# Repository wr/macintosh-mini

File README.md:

<h1 align="center"> Macintosh Mini</h1>

<p align="center">
  <strong>Turn a Maclock alarm clock into a working Mac with a Raspberry Pi</strong>
</p>

<p align="center">
  <a href="https://wells.ee/projects/macintosh-mini/?ref=gh-macintosh-mini">Build guide</a> ⬪
  <a href="#step-2-install-the-software">Install the software</a> ⬪
  <a href="https://shop.wells.ee/products/macintosh-mini/?ref=gh-macintosh-mini">Buy a kit</a> ⬪
  <a href="#donate">Donate</a>
</p>

<p align="center">
  
  <br />
  <a href="https://www.youtube.com/watch?v=zAbAf5-H5Yo">⏵ Watch the full build on YouTube</a>
</p>

---

## What is it?

A [Maclock](https://www.aliexpress.us/w/wholesale-maclock.html) is a cheap alarm clock built into a shockingly accurate miniature Macintosh shell. This project guts one and rebuilds it around a Raspberry Pi Zero running a 68k or PowerPC emulator, so the tiny Mac actually boots System 7, plays the startup chime, and runs vintage software. Buttons, brightness, sound, Wi-Fi, Bluetooth, and battery all work.

## Step 1: Build or buy one

The [build guide](https://wells.ee/projects/macintosh-mini/?ref=gh-macintosh-mini), on my site, covers everything from opening the clock to the first boot: parts, assembly, software, and troubleshooting.

You can [buy a DIY kit or a finished build](https://shop.wells.ee/products/macintosh-mini/?ref=gh-macintosh-mini) from my maker shop. Faster than shipping from China, and your purchase supports the continued development of this project.

## Step 2: Install the software

**You will need:**
- A Mac ROM file (`064DC91D` is a common one to search for)
- A Mac OS disk image with System 7.0 to 8.5. The [BlueSCSI image library](https://bluescsi.com/docs/BlueSCSI-Images) has ready-made ones, or skip it: the installer offers [our Mac OS 8.1 disk](https://archive.org/details/macos-8.1-basilisk-ii)

**Prepare the MicroSD card**
1. Flash **Raspberry Pi OS Lite (64-bit)** to a microSD card with [Raspberry Pi Imager](https://www.raspberrypi.com/software/). Set your Wi-Fi network and turn on SSH in its settings.
2. Rename your Mac ROM file to `ROM`, and copy it and your disk image, if you have one, to the Pi's home folder:

   ```bash
   scp ROM yourdisk.hda <user>@<pi_ip>:~/
   ```

3. SSH into the Pi and run the install script. It asks a few questions, like which startup chime to play, then does the rest:

   ```bash
   curl -fsSL https://raw.githubusercontent.com/wr/macintosh-mini/main/setup.sh | bash
   ```

The Pi automatically restarts into Mac OS when it's done.

You can run the same command again to install future updates.

* * *

_Optional:_ If you want to skip the automatic script and install everything yourself, or see exactly what the script changes:

- [Set up the Pi](maclock-build/): display, audio, brightness dial and buttons.
-  [Install the emulator](emulators/): Basilisk II or SheepShaver.

## Getting help

Open a [GitHub issue](https://github.com/wr/macintosh-mini/issues) — I'm happy to help, and very responsive!

## Credits

Startup chimes and crash sounds are mirrored from D. Schaub's Apple Sounds collection at <https://froods.ca/~dschaub/sound.html>. All sounds are © Apple, Inc.

## Donate

While this project is free and open source, donations are deeply appreciated, and make ongoing development and support possible.
[Donate now](https://www.buymeacoffee.com/wellsworkshop)

## License

Copyright © 2026 Wells Riley.

- **Hardware** (the boards, the bezel and the USB port jig): [CERN-OHL-S-2.0](./LICENSES/CERN-OHL-S-2.0.txt)
- **Software** ([`setup.sh`](./setup.sh) and [`maclock-build/`](./maclock-build/)): [GPL-3.0-or-later](./LICENSES/GPL-3.0-or-later.txt)
- **Everything else** (docs, drawings, photos): [CC BY-SA 4.0](./LICENSES/CC-BY-SA-4.0.txt)

The [Mac chimes](./emulators/chimes/) are Apple's and the display overlay is Waveshare's; neither is covered. [`REUSE.toml`](./REUSE.toml) maps every file.

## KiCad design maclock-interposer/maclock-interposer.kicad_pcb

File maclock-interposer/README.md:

# Macintosh Mini GPIO interposer

A 52 × 27.4 mm, 2-layer KiCad 10 board that sits on the 40-pin header between the Pi Zero 2 W and the Waveshare 2.8" DPI display. Order it fully assembled — no soldering, and no bent, cut, or desoldered pins on the Pi.

An SMD socket underneath plugs onto the Pi and an SMD pin header on top plugs into the display. 35 pins pass straight through (one via each); the five GPIOs the [breakout PCB](../maclock-pcb/) uses (header pins 13, 19, 23, 35, 37) connect to the Pi side **only** and never reach the display, which otherwise fights the dial and buttons. Those five plus 5V and GND come out on a straight 1×7 female socket (J2) on the screen side at the GPIO 21 end, in the same order as the breakout's `Pi GPIO` header, so one straight 1×7 male-to-female Dupont cable connects the two.

The board is drawn the way it sits in the Maclock: Pi mounted upside-down, seen from the screen. Order it with **blue solder mask and white silkscreen** — the screen side is inverted (silk is the background, the lettering is bare mask); branding is on the Pi side, and J2's pin labels are on both sides.

| J2 pin | Silk   | Net   | Pi header pin | GPIO |
| ------ | ------ | ----- | ------------- | ---- |
| 1      | Dial B | ENC_B | 19            | 10   |
| 2      | GND    | GND   | 20 (all GNDs) | —    |
| 3      | Dial A | ENC_A | 23            | 11   |
| 4      | 5V     | 5V    | 2, 4          | —    |
| 5      | A+     | AUDIO | 35            | 19   |
| 6      | SW2    | BTN2  | 37            | 26   |
| 7      | SW1    | BTN1  | 13            | 27   |

## Bill of materials

| Ref | Qty | Part                                                                  | LCSC                                                                  | Notes                                             |
| --- | --- | --------------------------------------------------------------------- | --------------------------------------------------------------------- | ------------------------------------------------- |
| J1  | 1   | 2×20 female socket, 2.54 mm, SMD, 8.5 mm — Hong Cheng `HC-PM254-8.5H-2x20PS` | [`C22436166`](https://www.lcsc.com/product-detail/C22436166.html) | **Bottom** side, plugs onto the Pi                |
| J3  | 1   | 2×20 pin header, 2.54 mm, SMD — Hanbo `HB-PH9-254220PB2GOP`            | [`C6332245`](https://www.lcsc.com/product-detail/C6332245.html)       | Top side, plugs into the display                  |
| J2  | 1   | 1×7 female header (socket), 2.54 mm, 8.5 mm, THT — XFCN `PM254V-11-07-H85` | [`C2832270`](https://www.lcsc.com/product-detail/C2832270.html) | Top (screen) side |

Both sides carry parts, so order two-sided assembly. Before ordering, check the J1/J3 drawings for locating pegs — the footprints are KiCad's generic peg-less SMD lands (3.0 / 3.15 × 1.0 mm pads, ±2.52 mm from the centreline).

## Use

Stack Pi → interposer → display (silk: `THIS SIDE FACING PI` / `THIS SIDE FACING SCREEN`). Run a straight 1×7 male-to-female Dupont cable from J2 to the breakout's `Pi GPIO` header, pin 1 (`Dial B`, square pad, GPIO 21 end) to pin 1 (`Dial B`).

The interposer adds about 12.5 mm between the Pi and the display (8.5 mm socket + 1.6 mm PCB + 2.5 mm header base), and the board reaches ~10.5 mm past the Pi's header edge. J2 stands 8.5 mm off the screen side, and the Dupont plug in it points toward the display — check both against your case and the display board before ordering.

## License

CERN-OHL-S-2.0, same as the [breakout PCB](../maclock-pcb/README.md#license) — see [`LICENSE`](./LICENSE).

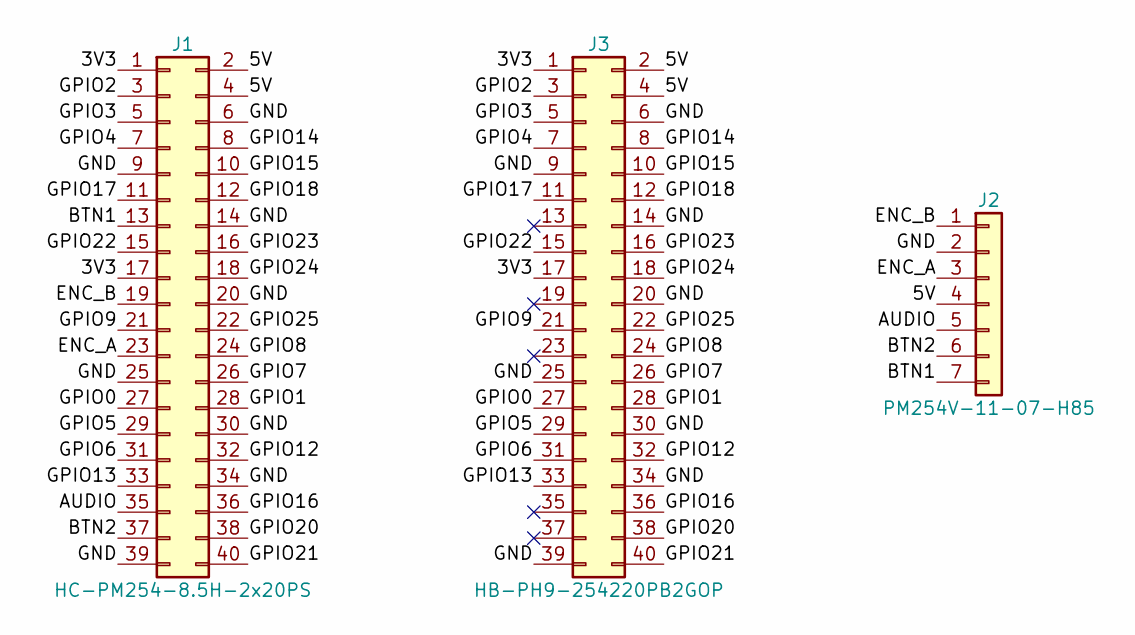
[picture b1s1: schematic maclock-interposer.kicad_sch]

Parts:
J1: HC-PM254-8.5H-2x20PS; PinSocket_2x20_P2.54mm_Vertical_SMD; MPN HC-PM254-8.5H-2x20PS; LCSC C22436166
J2: PM254V-11-07-H85; PinSocket_1x07_P2.54mm_Vertical; MPN PM254V-11-07-H85; LCSC C2832270
J3: HB-PH9-254220PB2GOP; PinHeader_2x20_P2.54mm_Vertical_SMD; MPN HB-PH9-254220PB2GOP; LCSC C6332245

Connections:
/3V3: J1.1, J1.17, J3.1, J3.17
/5V: J1.2, J1.4, J2.4, J3.2, J3.4
/AUDIO: J1.35, J2.5
/BTN1: J1.13, J2.7
/BTN2: J1.37, J2.6
/ENC_A: J1.23, J2.3
/ENC_B: J1.19, J2.1
/GND: J1.6, J1.9, J1.14, J1.20, J1.25, J1.30, J1.34, J1.39, J2.2, J3.6, J3.9, J3.14, J3.20, J3.25, J3.30, J3.34, J3.39
/GPIO0: J1.27, J3.27
/GPIO1: J1.28, J3.28
/GPIO2: J1.3, J3.3
/GPIO3: J1.5, J3.5
/GPIO4: J1.7, J3.7
/GPIO5: J1.29, J3.29
/GPIO6: J1.31, J3.31
/GPIO7: J1.26, J3.26
/GPIO8: J1.24, J3.24
/GPIO9: J1.21, J3.21
/GPIO12: J1.32, J3.32
/GPIO13: J1.33, J3.33
/GPIO14: J1.8, J3.8
/GPIO15: J1.10, J3.10
/GPIO16: J1.36, J3.36
/GPIO17: J1.11, J3.11
/GPIO18: J1.12, J3.12
/GPIO20: J1.38, J3.38
/GPIO21: J1.40, J3.40
/GPIO22: J1.15, J3.15
/GPIO23: J1.16, J3.16
/GPIO24: J1.18, J3.18
/GPIO25: J1.22, J3.22

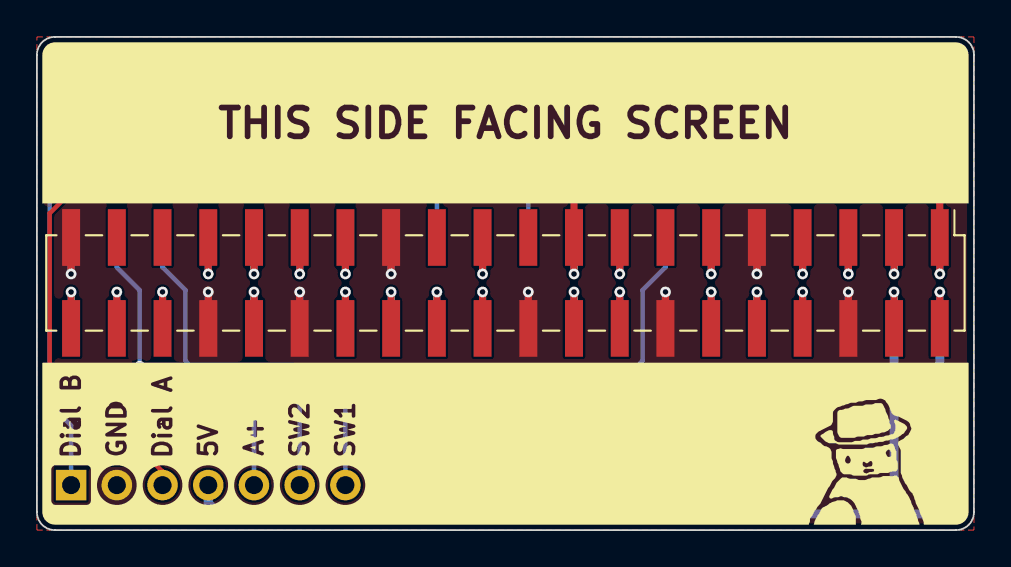
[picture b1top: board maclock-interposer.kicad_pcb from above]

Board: 2 copper layers, 52.1 x 27.4 mm, 3 parts (1 on the bottom side), 31 nets.

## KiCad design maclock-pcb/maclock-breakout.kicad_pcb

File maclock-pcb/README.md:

# Macintosh Mini breakout PCB

KiCad 10 project for the breakout that connects the Mac-shaped clock's front-panel parts (rotary encoder, two pushbuttons, speaker, power switch and battery harness) to the Pi Zero 2 W. The PAM8302A audio amplifier is on the board itself. Current revision: 2026.11, which rebuilds the Pi's audio signal on the board and gives the Pi's supply current its own ground return (see [Design notes](#design-notes)); rev 2026.09 boards, the ones that shipped, work but whine faintly with the Pi running.

Wiring it to the Pi, with pin assignments, is [step 2 of the build guide](https://wells.ee/projects/macintosh-mini/#2-connect-the-pi-to-the-screen-and-the-board). For the case-side parts you'll print, see the [3D-printed screen bezel](../maclock-screen-bezel/).

Order from [PCBway](https://www.pcbway.com/project/shareproject/W654223ASS41_Untitled_kicad_pcb_95cca7e3.html). You can [use my referral code](https://pcbway.com/g/AsfKU9) to get $5 off your order, if you want.

## Bill of materials

To populate one board. Every part except ENC1 is stocked at LCSC, so PCBway can assemble the board with ENC1 left off; it is out of the BOM and placement files, so fit it yourself afterwards. Only the Pi header is through-hole. The DigiKey column is for hand assembly: where DigiKey does not carry the LCSC part, a drop-in equivalent is named.

| Ref | Qty | Part | DigiKey (hand assembly) | Notes |
| --- | --- | --- | --- | --- |
| C1 | 1 | 10 nF X7R 0603 — FH `0603B103K500NT` (LCSC [`C57112`](https://www.lcsc.com/product-detail/C57112.html)) | [`1276-1009-1-ND`](https://www.digikey.com/en/products/result?keywords=1276-1009-1-ND) Samsung `CL10B103KB8NNNC` | Audio low-pass with R3 |
| C2, C3 | 2 | 220 nF X7R 0603 — Samsung `CL10B224KA8NNNC` (LCSC [`C21120`](https://www.lcsc.com/product-detail/C21120.html)) | [`1276-1111-1-ND`](https://www.digikey.com/en/products/result?keywords=1276-1111-1-ND) | Amp input coupling (IN+ and IN−) |
| C4, C8, C10 | 3 | 1 µF X5R 0603 — Samsung `CL10A105KB8NNNC` (LCSC [`C15849`](https://www.lcsc.com/product-detail/C15849.html)) | [`478-KGM15BR51E105KTCT-ND`](https://www.digikey.com/en/products/result?keywords=478-KGM15BR51E105KTCT-ND) KYOCERA AVX `06033D105KAT2A` (25 V) | Amp supply decoupling (C4); U3 input (C8); U3 output and U2 supply (C10) |
| C5 | 1 | 10 µF X5R 0805 — Samsung `CL21A106KAYNNNE` (LCSC [`C15850`](https://www.lcsc.com/product-detail/C15850.html)) | [`490-16824-1-ND`](https://www.digikey.com/en/products/result?keywords=490-16824-1-ND) Murata `GRM21BR61E106KA73K` | Amp bulk decoupling |
| C6 | 0 | 470 pF C0G 0402 — Samsung `CL05C471JB5NNNC` (LCSC [`C307449`](https://www.lcsc.com/product-detail/C307449.html)) | [`1276-1117-1-ND`](https://www.digikey.com/en/products/result?keywords=1276-1117-1-ND) | **Not fitted**, left off the BOM and placement file. Optional second filter pole across the amp inputs, between R4 and R5 (see [Design notes](#design-notes)) |
| ENC1 | 1 | Rotary encoder, HUANO 4.5 mm mouse-wheel type, laid on its back with the hex bore up — sold as MECCANIXITY on [Amazon](https://www.amazon.com/dp/B0C13ZZVT5) (10-pack) and on [AliExpress](https://www.aliexpress.us/item/3256805576298875.html) (choose 4.5MM); not stocked at LCSC, DigiKey or Mouser | — (no equivalent at DigiKey) | The dial. Body 9.54 × 8.34 × 4.15 mm, 1.74 mm hex bore, 2.5 mm pin pitch. **Fitted by hand**, left out of the BOM and placement file: lay it on its black back over the bore with the marked metal face up and the pins north, bend the pins down onto their pads and solder, and do the same with the two clip legs on the MP pads for strength. Seen from the marked face with the pins down, the common pin is on the left, as on TT's and HOAUC's mouse-wheel encoders, so face up it lands on C, the east pad |
| J1 | 1 | Molex PicoBlade 1×2, 1.25 mm, SMD top entry — `53398-0271` (LCSC [`C122410`](https://www.lcsc.com/product-detail/C122410.html)) | [`WM7606CT-ND`](https://www.digikey.com/en/products/result?keywords=WM7606CT-ND) | **Power switch**, in series with the battery supply; silkscreened "Switch". Takes the Maclock's 2-wire switch plug |
| J2 | 1 | Molex PicoBlade 1×4, 1.25 mm, SMD top entry — `53398-0471` (LCSC [`C17617036`](https://www.lcsc.com/product-detail/C17617036.html)) | [`WM7608CT-ND`](https://www.digikey.com/en/products/result?keywords=WM7608CT-ND) | **Power input**, silkscreened "Power". Takes the Maclock's 4-wire plug: pin 1 (silk `+`) = battery supply, about 4 V (the clock's charging board passes the cell through, it does not boost it), pin 2 (silk `-`) = GND, pins 3–4 unused |
| J3 | 1 | Molex PicoBlade 1×2, 1.25 mm, SMD top entry — `53398-0271` (LCSC [`C122410`](https://www.lcsc.com/product-detail/C122410.html)) | [`WM7606CT-ND`](https://www.digikey.com/en/products/result?keywords=WM7606CT-ND) | **Speaker**, silkscreened "Speaker". Same part as J1; polarity does not matter |
| J4 | 1 | 1×7 male pin header, 2.54 mm — XFCN `PZ254V-11-07P` (LCSC [`C492406`](https://www.lcsc.com/product-detail/C492406.html)) | [`35-PRPC007SAAN-RC-ND`](https://www.digikey.com/en/products/result?keywords=35-PRPC007SAAN-RC-ND) Sullins `PRPC007SAAN-RC` | Through-hole, silkscreened "Pi GPIO". Pin order: Dial B, GND, Dial A, 5V, A+, SW2, SW1 |
| R1, R2 | 2 | 1 kΩ ±1% 0402 — UNI-ROYAL `0402WGF1001TCE` (LCSC [`C11702`](https://www.lcsc.com/product-detail/C11702.html)) | [`311-1.00KLRCT-ND`](https://www.digikey.com/en/products/result?keywords=311-1.00KLRCT-ND) Yageo `RC0402FR-071KL` | In series with the SW1 and SW2 button lines |
| R3 | 1 | 1 kΩ ±1% 0402 — same as above | same as above | With C1, the 16 kHz low-pass on the rebuilt PWM audio |
| R4, R5 | 2 | 47 kΩ ±1% 0402 — UNI-ROYAL `0402WGF4702TCE` (LCSC [`C25792`](https://www.lcsc.com/product-detail/C25792.html)) | [`311-47.0KLRCT-ND`](https://www.digikey.com/en/products/result?keywords=311-47.0KLRCT-ND) Yageo `RC0402FR-0747KL` | Amp input resistors, set the gain to about 8 dB |
| R6 | 1 | 100 kΩ ±1% 0402 — UNI-ROYAL `0402WGF1003TCE` (LCSC [`C25741`](https://www.lcsc.com/product-detail/C25741.html)) | [`311-100KLRCT-ND`](https://www.digikey.com/en/products/result?keywords=311-100KLRCT-ND) Yageo `RC0402FR-07100KL` | Pull-up on the amp's shutdown pin (amp always on) |
| SW1, SW2 | 2 | BZCN `TSB001A3518A` side-press SMD tactile, 7.7 × 3.55 mm, 180 gf (LCSC [`C2888448`](https://www.lcsc.com/product-detail/C2888448.html)) | [`2223-TS32-7-35-BK-B-160-RA-SMT-TRCT-ND`](https://www.digikey.com/en/products/result?keywords=2223-TS32-7-35-BK-B-160-RA-SMT-TRCT-ND) Same Sky `TS32-7-35-BK-B-160-RA-SMT-TR`: same land (its pegs, shell pads and 4.2 mm signal pitch match; the signal pads sit 0.15 mm closer to the pegs), but 160 gf, and the button sits about 0.15 mm lower and 0.2 mm further out. Not yet tried in the case | The two front buttons |
| U1 | 1 | PAM8302A 2.5 W class-D mono amp, MSOP-8 — Diodes `PAM8302AASCR` (LCSC [`C113367`](https://www.lcsc.com/product-detail/C113367.html)) | [`PAM8302AASCRDICT-ND`](https://www.digikey.com/en/products/result?keywords=PAM8302AASCRDICT-ND) | Bottom side |
| U2 | 1 | Single Schmitt-trigger buffer, SOT-23-5 — TI `SN74LVC1G17DBVR` (LCSC [`C7836`](https://www.lcsc.com/product-detail/C7836.html)) | [`296-11933-1-ND`](https://www.digikey.com/en/products/result?keywords=296-11933-1-ND) | Rebuilds the Pi's PWM audio from U3's 3.0 V |
| U3 | 1 | 3.0 V low-noise LDO, SOT-23-5 — TI `TPS7A2030PDBVR` (LCSC [`C963429`](https://www.lcsc.com/product-detail/C963429.html)) | [`296-TPS7A2030PDBVRCT-ND`](https://www.digikey.com/en/products/result?keywords=296-TPS7A2030PDBVRCT-ND) | Quiet 3.0 V for U2 and the shutdown pull-up |
| — | 1 | Small speaker, 8 Ω, 1 W, 28–40 mm, PicoBlade 1.25 mm 2-pin plug (often sold as "JST 1.25"), e.g. [Adafruit 3923](https://www.adafruit.com/product/3923) | — | Whatever fits behind the Maclock grille |

The schematic carries the same data in each symbol's `Manufacturer`, `MPN`, `LCSC` and (for ENC1) `Supplier` / `Supplier Link` fields, so any BOM exported from it includes ENC1's source, though ENC1 itself is left out of the BOM.

## Design notes

**Audio input.** The Pi's audio is PWM on GPIO 19, switching between the Pi's own 3.3 V and ground, so it carries whatever noise the Pi's supply and ground do. U2 rebuilds it from U3, a separate low-noise 3.0 V regulator (net `+3V0`), so only the timing of the Pi's signal reaches the amp. U3 runs from the clock's battery, which is about 4 V at full charge and falls as it drains, so it is a 3.0 V part rather than 3.3 V: that keeps it far enough above its dropout to keep filtering as the battery runs down. It works just as well from a real 5 V. R3/C1 then low-pass it at 16 kHz.

**Amplifier.** The filtered signal goes C2 → R4 → PAM8302A IN+, with IN− terminated through the matching R5/C3 pair. R4 adds to the chip's internal 10 kΩ input resistor, which brings its fixed 23.5 dB gain down to about 8 dB; fine volume is a software setting, and `setup.sh` leaves 4 dB of headroom so the startup chime's peaks don't clip. The shutdown pin is pulled up through R6 so the amp is always on (no header GPIO is free for a mute).

C6 is a spare pad, not fitted. R3/C1 is a single pole, which takes only about 24 dB off the Pi's PWM noise near the amp's own 200–300 kHz switching frequency, where a class-D amp can fold it back into the audio band as hiss or a faint whistle. A 470 pF across IN+ and IN− adds a second pole at about 20 kHz (with R4/R5 and the chip's internal 10 kΩ), for roughly 46 dB there, at the cost of about 1 dB at 10 kHz. The rev 2026.09 boards have the same single pole and none of their measured noise came from it, so solder C6 on only if a board hisses or whistles with the amp warm.

**Grounds.** The Pi, its display and its backlight draw up to about 1 A, and the return current comes back on its own trace (net `GND_PI`) from J4 pin 2 to J2, where the net tie NT1 joins it to the board ground. On earlier revisions that current flowed through the amp's ground and the amp shared the Pi's supply copper, which put a faint whine in the speaker of the rev 2026.09 boards: a 1 kHz comb from the backlight PWM, plus drifting tones from the emulator's load. NT1 is copper only, so it is not in the BOM. The amp now takes its supply straight from J1, so it no longer shares the Pi's supply trace, and its 1 µF decoupling capacitor sits right against its supply and ground pins.

**Dial and buttons.** ENC1's A and B go straight to GPIO 11 and GPIO 10, and the buttons through R1/R2 to GPIO 27 and GPIO 26; the Pi's internal pull-ups do the rest (see [`brightness_control.py`](../maclock-build/brightness_control.py)). ENC1 lies on its back with its bore over the dial's shaft and its pins pointing north; its footprint origin is the bore. HUANO publishes no drawing, so the land is drawn from a measured part: the bore is 4.5 mm from the pin edge and the pins are 3 mm long, and the pads run from just outside the body to the pin tips. Lying flat, it stands 4.15 mm tall.

**Libraries.** Two project libraries ship with the board, next to the KiCad 10 standard libraries:

- `maclock` — ENC1's symbol and footprint, drawn for this project because the encoder lies on its back and has no published land pattern. There is no 3D model for it.
- `lcsc` — LCSC's own symbol, footprint and 3D model for SW1/SW2 (C2888448), imported with `easyeda2kicad --full --lcsc_id=C2888448`. easyeda2kicad's conversion artefacts were fixed, nothing else: the plastic-peg holes are NPTH, the bracket pads have no outline stroke (so the copper is LCSC's 1.5 mm), the pins are passive, and the courtyard is one closed outline.

## Fabrication files

Gerbers, drill files, the placement file and the BOM are generated with `kicad-cli` into `production/`, which git ignores:

```sh
K=/Applications/KiCad/KiCad.app/Contents/MacOS/kicad-cli
mkdir -p production/gerbers
$K pcb export gerbers -l "F.Cu,B.Cu,F.Paste,B.Paste,F.Silkscreen,B.Silkscreen,F.Mask,B.Mask,Edge.Cuts" -o production/gerbers/ maclock-breakout.kicad_pcb
$K pcb export drill --format excellon --excellon-separate-th -o production/gerbers/ maclock-breakout.kicad_pcb
(cd production && zip -qj maclock-breakout-gerbers.zip gerbers/* && rm -r gerbers)
$K pcb export pos --format csv --units mm --side both -o production/maclock-breakout-positions.csv maclock-breakout.kicad_pcb
$K sch export bom --fields 'Reference,${QUANTITY},Value,Footprint,Manufacturer,MPN,LCSC,Supplier,Supplier Link' \
  --group-by 'Value,Footprint,MPN' -o production/maclock-breakout-bom.csv maclock-breakout.kicad_sch
```

## License

CERN-OHL-S-2.0 — see [`LICENSE`](./LICENSE). You can make, modify and sell the board. Boards you make must point to their source, and a modified design must be published under the same licence.

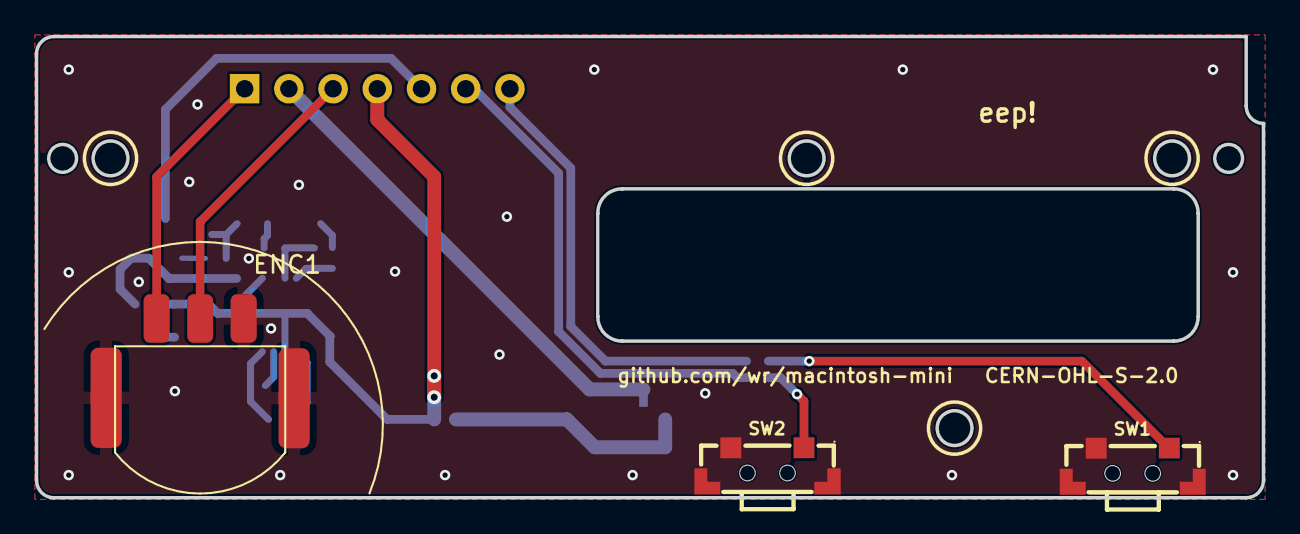
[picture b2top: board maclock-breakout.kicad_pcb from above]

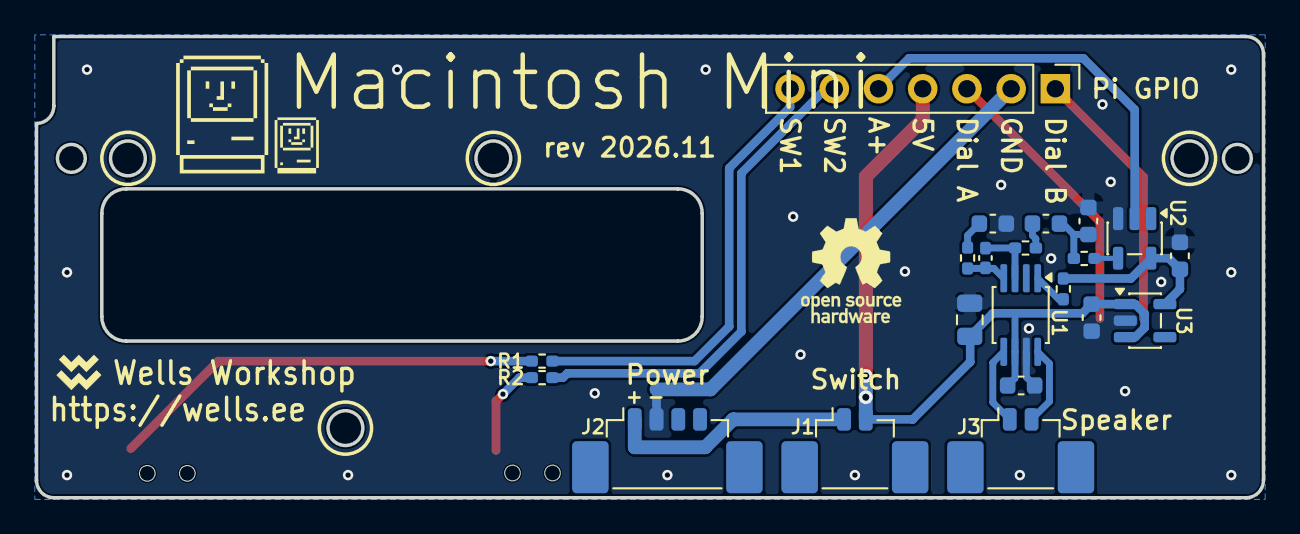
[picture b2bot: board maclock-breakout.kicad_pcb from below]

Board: 2 copper layers, 70.5 x 26.5 mm, 26 parts (23 on the bottom side), 21 nets.

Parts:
C1: 10nF; C_0603_1608Metric
C2, C3: 220nF; C_0603_1608Metric
C4, C8, C10: 1uF; C_0603_1608Metric
C5: 10uF; C_0805_2012Metric
C6: 470pF; C_0402_1005Metric_Pad0.74x0.62mm_HandSolder
ENC1: HUANO 4.5; RotaryEncoder_HUANO_4.5mm_LayFlat_SMD
J1, J3: 53398-0271; Molex_PicoBlade_53398-0271_1x02-1MP_P1.25mm_Vertical
J2: 53398-0471; Molex_PicoBlade_53398-0471_1x04-1MP_P1.25mm_Vertical
J4: Pi GPIO; PinHeader_1x07_P2.54mm_Vertical
LOGO1: OSHW-Logo_5.7x6mm_SilkScreen
NT1: NetTie_2; NetTie-2_SMD_Pad0.5mm
R1, R2, R3: 1k; R_0402_1005Metric_Pad0.72x0.64mm_HandSolder
R4, R5: 47k; R_0402_1005Metric_Pad0.72x0.64mm_HandSolder
R6: 100k; R_0402_1005Metric_Pad0.72x0.64mm_HandSolder
SW1, SW2: TSB001A3518A; SW-SMD_TSB001XXXX
U1: PAM8302AASCR; MSOP-8_3x3mm_P0.65mm
U2: SN74LVC1G17DBVR; SOT-23-5
U3: TPS7A2030PDBVR; SOT-23-5

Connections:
+3V0: C10.1, R6.1, U2.5, U3.5
+5V: C4.1, C5.1, C8.1, J1.2, J4.4, U1.6, U3.1, U3.3
/5V_IN: J1.1, J2.1
/A+: C1.1, C2.1, R3.2
/AMP_SD: R6.2, U1.1
/AUDIO: J4.5, U2.2
/BTN1: J4.7, R1.1
/BTN2: J4.6, R2.1
/ENC_A: ENC1.A, J4.3
/ENC_B: ENC1.B, J4.1
/GND_PI: J4.2, NT1.1
/SPK+: J3.1, U1.5
/SPK-: J3.2, U1.8
/SW1: R1.2, SW1.1
/SW2: R2.2, SW2.1
GND: C1.2, C3.1, C4.2, C5.2, C8.2, C10.2, ENC1.C, ENC1.MP, J2.2, NT1.2, SW1.2, SW1.3, SW1.4, SW2.2, SW2.3, SW2.4, U1.7, U2.3, U3.2
unnamed: C2.2, R4.1
unnamed: C3.2, R5.1
unnamed: R3.1, U2.4
unnamed: C6.1, R4.2, U1.3
unnamed: C6.2, R5.2, U1.4

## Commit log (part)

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2026-05-14 updated board design to 2026.5
2026-05-28 Add BasiliskII (68k) install path for leaner emulation on Pi Zero 2 W
    SheepShaver interprets PowerPC on the Zero 2 W's Cortex-A53 (its JIT is
    x86-only), which is the worst case for this hardware. Emulating a 68k Mac
    (System 7) via BasiliskII is far cheaper to interpret, so add it as a
    parallel install path and make it the default in the menu, keeping
    SheepShaver selectable for PPC-era software.
    Tuning follows the proven MacintoshPi-on-Zero-2-W config: frameskip 2,
2026-05-28 BasiliskII: add --rom flag, libmpfr-dev dep, autostart switching, debug-exit fix
    Shaken out by an end-to-end install on the actual Pi Zero 2 W:
    - --rom <file>: a Pi may already hold a 4 MB PPC ROM named "ROM"; the 68k
    ROM needs explicit selection (the default "ROM" would be the wrong one).
    - libmpfr-dev: BasiliskII's FPU core compiles with -DFPU_MPFR and won't
    build on a fresh Pi without the MPFR headers.
    - Each emulator's profile patch now strips the other's autostart block, so
2026-05-28 Add kiosk lifecycle controls; make re-runs update/switch-safe
    - Reset button double-press force-quits the emulator to a Pi prompt;
    button_handler gains debounce-aware single vs double dispatch.
    - Launcher keys off the emulator's exit status: 0 (Mac "Shut Down") or
    143 (double-reset) drop to a Pi prompt, anything else relaunches.
    Mac "Restart" reboots the VM in place, so it auto-reboots for free.
    - Add a `macintosh` command to (re)boot the Mac from a shell.
2026-05-28 Enable VOSF for BasiliskII
    VOSF re-blits only changed screen regions instead of the whole frame
    every tick — noticeably snappier UI. Verified stable on the Pi Zero 2 W
    (aarch64), so drop the old --disable-vosf workaround.
    Refs: W-247
2026-05-28 Add boot preflight for missing/unconfigured ROM or disk
    New /usr/local/bin/mac-preflight runs before the emulator: if the
    configured ROM+disk are present it boots; if not, it auto-fills the
    prefs when exactly one ROM (matched by size) and one disk image exist
    in $HOME; otherwise it prints what's missing/ambiguous and drops to a
    prompt instead of failing cryptically. Wired into both launchers.
    Refs: W-247, W-266
2026-05-28 README: list which disk image formats work
    Most people grab an image online; spell out what mounts (raw hard-disk
    images, any extension; sparsebundle) and what doesn't (.dmg/.smi/.toast,
    still-zipped files).
    Refs: W-247
2026-05-28 Reorganize emulator guides into emulators/; default networking
    - Move the manual guides into emulators/ (SheepShaver.md, BasiliskII.md)
    next to the shared chimes/, with an index README. Adds a BasiliskII
    manual guide that was missing.
    - Add `ether slirp` to both prefs so networking works out of the box.
    - Accuracy + path fixes across all READMEs (BasiliskII is the default,
    button single/double behavior, disk formats, updated cross-links and
2026-05-28 Tidy manual-install wording in READMEs
    Bullet the root README's manual-install guide links and trim the
    maclock-build emulator paragraph.
    Refs: W-247
2026-05-28 Stop tracking KiCad fp-lib-table
    It pinned KiCad to a machine-specific absolute path. Remove it and
    gitignore the project-local KiCad lib tables.
2026-05-28 Add BasiliskII (68k) emulator as default
    * Add BasiliskII (68k) install path for leaner emulation on Pi Zero 2 W
    SheepShaver interprets PowerPC on the Zero 2 W's Cortex-A53 (its JIT is
    x86-only), which is the worst case for this hardware. Emulating a 68k Mac
    (System 7) via BasiliskII is far cheaper to interpret, so add it as a
    parallel install path and make it the default in the menu, keeping
    SheepShaver selectable for PPC-era software.
2026-05-28 setup: clearer install menu
    Replace the cryptic "Both" default with self-describing options, a blank
    separator after the recommended choice, and widen the menu box to fit.
    Refs: W-269
2026-05-28 docs: write the product name as "Basilisk II" (with a space)
    Apply the spaced name in user-facing prose and the install-menu labels.
    The binary, paths, commands, and the BasiliskII.md filename/links are
    left as-is.
    Refs: W-269
2026-05-28 setup: reconfigure menu for existing installs
    When prefs already exist for the chosen emulator, offer a keep-or-change
    menu (disk image, startup chime, color depth) instead of silently keeping
    everything. Changes are applied in place; fresh-install flow unchanged.
    Refs: W-270
2026-05-28 setup: polish installer and settings menus
    - Install menu: title "Macintosh Mini Installer", no prompt line, no
    blank separator, shorter labels.
    - Emulator Settings: drop the "Keep" row; OK=<Change> the highlighted
    setting, Cancel=<Continue> to proceed; show current values; title
    "Emulator Settings". Persist the chosen chime so its value can show.
    - Shorten the performance prompt text.
2026-05-28 setup: colons + full labels in settings, clearer perf prompt
    Emulator Settings rows read "Disk image:/Startup chime:/Color depth:"
    with full color-depth text (e.g. "Black & White 1-bit"). Performance
    prompt retitled, prompt line dropped, options described plainly.
    Refs: W-269, W-270
2026-05-29 Clearer installer menu (#8)
    * setup: clearer install menu
    Replace the cryptic "Both" default with self-describing options, a blank
    separator after the recommended choice, and widen the menu box to fit.
    Refs: W-269
    * docs: write the product name as "Basilisk II" (with a space)
    Apply the spaced name in user-facing prose and the install-menu labels.
2026-05-29 setup: suppress emulator core dumps; check SheepShaver ROM size
    - ulimit -c 0 in both launchers — the reset button stops getty/cage out
    from under the emulator, which faults on teardown and dropped a 31 MB
    core in $HOME each press. Crash->relaunch still works; just no junk.
    - check_sheepshaver_assets now rejects a 512 KB/1 MB 68k ROM (needs the
    4 MB PowerPC ROM), mirroring the existing BasiliskII ROM check.
    Refs: W-271
2026-05-29 setup: suppress emulator core dumps; check SheepShaver ROM size (#9)
    - ulimit -c 0 in both launchers — the reset button stops getty/cage out
    from under the emulator, which faults on teardown and dropped a 31 MB
    core in $HOME each press. Crash->relaunch still works; just no junk.
    - check_sheepshaver_assets now rejects a 512 KB/1 MB 68k ROM (needs the
    4 MB PowerPC ROM), mirroring the existing BasiliskII ROM check.
    Refs: W-271
2026-05-29 setup: version the installer
    Add a VERSION constant (1.0.0) and surface it at startup — in the banner
    and the install-menu title ("Macintosh Mini Installer v1.0.0").
    Refs: W-272
2026-05-29 setup: version the installer (#10)
    Add a VERSION constant (1.0.0) and surface it at startup — in the banner
    and the install-menu title ("Macintosh Mini Installer v1.0.0").
    Refs: W-272
2026-06-01 Add pantry quick-reorder terminal (ESP32-S3 + LVGL touchscreen)
    A pantry touchscreen where tapping a product tile adds the item directly
    to your Amazon cart. Runs entirely on an ESP32-S3 with an LVGL display
    (default target: Elecrow ESP32-S3 3.5" Terminal) — no backend.
    Since Amazon has no consumer ordering API, the device authenticates as
    you by replaying stored session cookies against the add-to-cart endpoint,
    then you finish checkout from the Amazon app. Secrets (Wi-Fi + cookies)
2026-06-09 setup: prompt for BasiliskII modelid (5 vs 14); bump to 1.1.0
    System 7.5 and Mac OS 8 require modelid 14 (Quadra); 7.0/7.1 needs
    modelid 5 (Mac IIci). Previously hardcoded to 5, which sad-Macs on 7.5+.
    Adds a menu prompt during fresh installs and a "Mac model" row in the
    reconfigure menu for existing installs, plus a --modelid flag.

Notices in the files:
maclock-interposer/maclock-interposer.kicad_pcb:
github.com/wr/macintosh-mini CERN-OHL-S-2.0
maclock-pcb/maclock-breakout.kicad_pcb:
Licensed CERN-OHL-S-2.0
